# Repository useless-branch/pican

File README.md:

# pican
Hat for Raspberry Pi Zero with CAN and RS232

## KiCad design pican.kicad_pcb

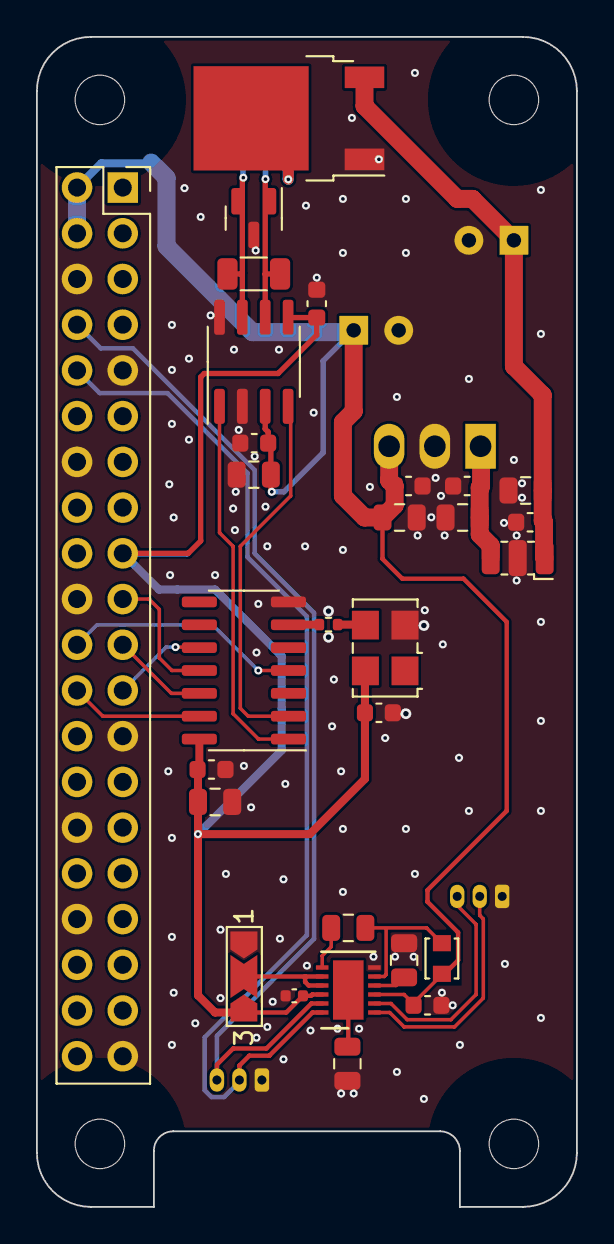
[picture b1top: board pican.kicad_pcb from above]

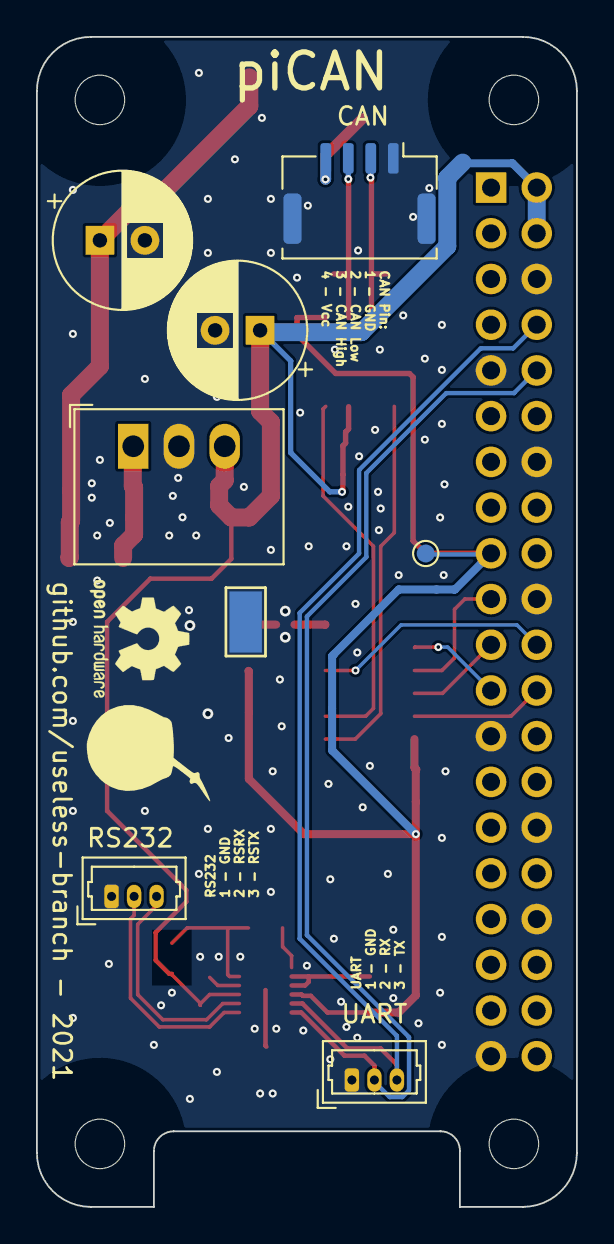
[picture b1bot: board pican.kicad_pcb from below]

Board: 4 copper layers, 30.0 x 65.0 mm, 37 parts (8 on the bottom side), 26 nets.

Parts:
C1: 100uF / 35V; CP_Radial_D7.5mm_P2.50mm
C2, C6: 4.7uF / 35V; C_0805_2012Metric
C3, C5, C9, C10, C12: 100nF / 10V; C_0603_1608Metric
C4, C7: 100nF / 35V; C_0603_1608Metric
C8, C11, C13: 4.7uF / 10V; C_0805_2012Metric
C14: 470uF / 10V; CP_Radial_D7.5mm_P2.50mm
C15: 220nF / 6.3 V; C_0402_1005Metric
C16: 220nF / 50 V; C_0805_2012Metric
C17, C18: 1uF / 24V; C_0805_2012Metric
C19: 1uF / 10 V; C_0603_1608Metric
D1: PESD2CAN; SOT-23
FL1: EMI_Filter_LCL; 3Pole_F1206
J1, J4: Uart; Molex_PicoBlade_53047-0310_1x03_P1.25mm_Vertical
J2: Conn_01x04_MountingPin; Molex_CLIK-Mate_502382-0470_1x04-1MP_P1.25mm_Vertical
J3: Raspberry_Pi_2_3; Raspberry_Pi_Zero_RightDesign
JP1: Jumper_3_Open; SolderJumper-3_P2.0mm_Open_TrianglePad1.0x1.5mm_NumberLabels
L1: 10u; L_Murata_LQH2MCNxxxx02_2.0x1.6mm
Q1: FDD4243; TO-252-2
R1: 33R; R_0402_1005Metric
R2: 120R; R_1206_3216Metric
TP1: +3V3; TestPoint_Pad_D1.0mm
TP2: GND; TestPoint_Keystone_5015_Micro-Minature
U1: R-78B5.0-2.0; Converter_DCDC_RECOM_R-78B-2.0_THT
U2: MCP2562FD-E-SN; SOIC-8_3.9x4.9mm_P1.27mm
U3: MCP2518FD-xSL; SOIC-14_3.9x8.7mm_P1.27mm
U4: LTC280X; DFN-12-1EP_3x4mm_P0.5mm_EP1.7x3.3mm
X1: SG-5032CCN; Oscillator_SMD_SeikoEpson_SG8002LB-4Pin_5.0x3.2mm

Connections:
+3V3: C3.1, C5.1, C11.2, C12.2, C15.2, J3.1 (3V3), J3.17 (3V3), JP1.3 (B), TP1.1, U2.5 (Vio), U3.14 (VDD), U4.10 (VL), X1.4 (Vcc)
+5V: C8.2, C9.2, C10.1, C13.2, C14.1, C19.1, J3.2 (5V), J3.4 (5V), L1.2, U1.3 (OUT), U2.3 (VDD), U4.3 (VCC)
+12V: C6.1, C7.1, FL1.3, U1.1 (IN)
/12V_IN: J2.4, Q1.2 (D)
/+12_F: C1.1, C2.2, C4.1, FL1.1, Q1.3 (S)
/CAN_H: D1.2 (K), J2.2, R2.1, U2.7 (CANH)
/CAN_L: D1.1 (K), J2.3, R2.2, U2.6 (CANL)
/CAN_RX: U2.4 (RXD), U3.2 (RXCAN)
/CAN_TX: U2.1 (TXD), U3.1 (TXCAN)
/INT: J3.22 (GPIO25), U3.4 (~INT)
/RSRX: J4.2, U4.1 (RIN)
/RSTX: J4.3, U4.2 (TOUT)
/RX: J1.2, J3.10 (GPIO15/RXD), U4.12 (ROUT)
/SPI_CE0: J3.24 (~CE0/GPIO8), U3.13 (nCS)
/SPI_MISO: J3.21 (MISO0/GPIO9), U3.12 (SDO)
/SPI_MOSI: J3.19 (MOSI0/GPIO10), U3.11 (SDI)
/SPI_SCLK: J3.23 (SCLK0/GPIO11), U3.10 (SCK)
/TX: J1.3, J3.8 (GPIO14/TXD), U4.11 (TIN)
GND: C1.2, C2.1, C3.2, C4.2, C5.2, C6.2, C7.2, C8.1, C9.1, C10.2, C11.1, C12.1, C13.1, C14.2, C15.1, C17.1, C18.1, C19.2, D1.3 (A), FL1.2, J1.1, J2.1, J2.MP (MountPin), J3.6 (GND), J3.9 (GND), J3.14 (GND), J3.20 (GND), J3.25 (GND), J3.30 (GND), J3.34 (GND), J3.39 (GND), J4.1, JP1.1 (A), Q1.1 (G), TP2.1, U1.2 (GND), U2.2 (VSS), U2.8 (STBY), U3.7 (VSS), U4.6 (GND), X1.2 (GND)
unnamed: C16.1, U4.7 (CAP)
unnamed: C16.2, L1.1, U4.5 (SW)
unnamed: C17.2, U4.13 (VEE)
unnamed: C18.2, U4.4 (VDD)
unnamed: JP1.2 (C), U4.8 (PS), U4.9 (MODE)
unnamed: R1.1, U3.6 (OSC1)
unnamed: R1.2, X1.3 (OUT)

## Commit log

2021-11-14 initial commit - project done
2021-11-14 board nearly finished
2021-11-15 generated bom
2021-11-15 researched parts
2021-11-16 updated board with new connector
2021-11-19 some stuff!
2021-12-01 changed crystal to osc
